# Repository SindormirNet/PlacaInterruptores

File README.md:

PlacaInterruptores
==================

  Placa de interruptores para clases de microcontroladores y electrónica digital  http://sindormir.net

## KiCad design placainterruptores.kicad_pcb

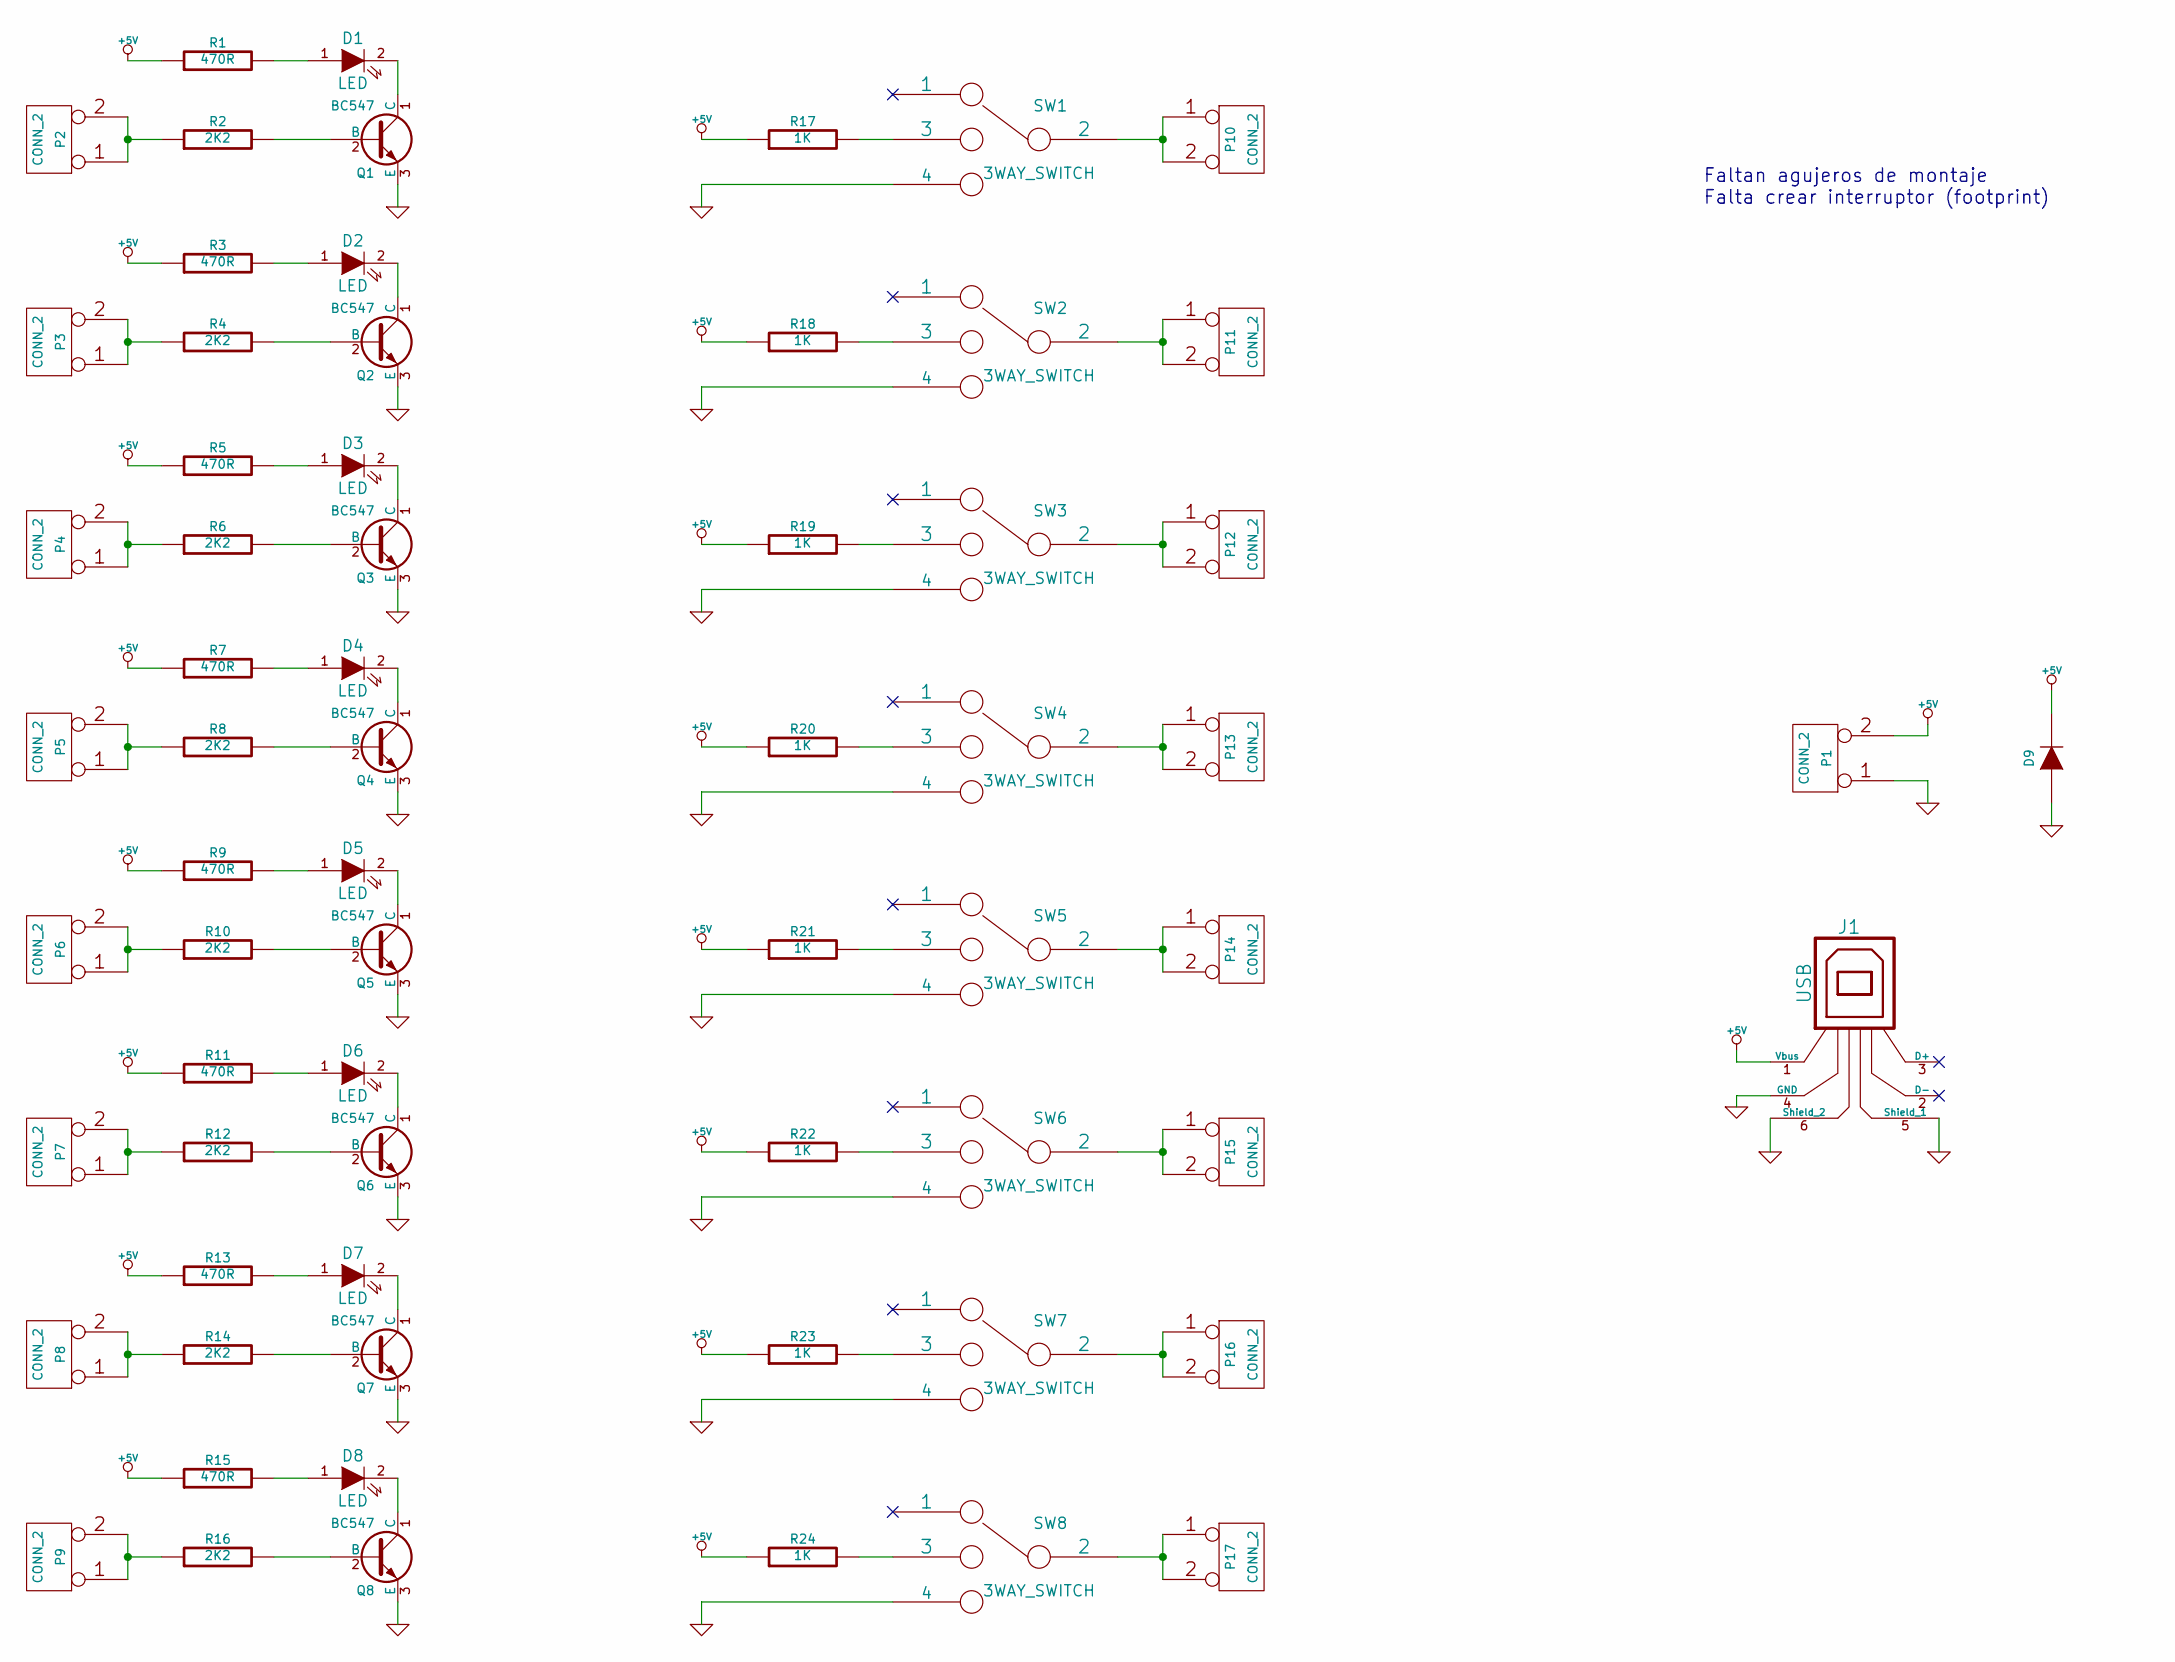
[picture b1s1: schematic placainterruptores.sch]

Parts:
D1, D2, D3, D4, D5, D6, D7, D8: LED; LED-0805
D9: DIODE; D3
J1: USB; USB_MINI_B
P1: CONN_2; 2PIN_6mm
P2, P3, P4, P5, P6, P7, P8, P9, P10, P11, P12, P13, P14, P15, P16, P17: CONN_2; SIL-2
Q1, Q2, Q3, Q4, Q5, Q6, Q7, Q8: BC547; TO92-123
R1, R3, R5, R7, R9, R11, R13, R15: 470R; R_0805
R2, R4, R6, R8, R10, R12, R14, R16: 2K2; R_0805
R17, R18, R19, R20, R21, R22, R23, R24: 1K; R_0805
SW1, SW2, SW3, SW4, SW5, SW6, SW7, SW8: 3WAY_SWITCH; 3WAY-SWITCH

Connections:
+5V: D9.2 (K), J1.1 (Vbus), P1.2 (PM), R1.1, R3.1, R5.1, R7.1, R9.1, R11.1, R13.1, R15.1, R17.1, R18.1, R19.1, R20.1, R21.1, R22.1, R23.1, R24.1
GND: D9.1 (A), J1.4 (GND), J1.5 (Shield_1), J1.6 (Shield_2), P1.1, Q1.3 (E), Q2.3 (E), Q3.3 (E), Q4.3 (E), Q5.3 (E), Q6.3 (E), Q7.3 (E), Q8.3 (E), SW1.4, SW2.4, SW3.4, SW4.4, SW5.4, SW6.4, SW7.4, SW8.4
unnamed: D1.1 (A), R1.2
unnamed: D1.2 (K), Q1.1 (C)
unnamed: D2.1 (A), R3.2
unnamed: D2.2 (K), Q2.1 (C)
unnamed: D3.1 (A), R5.2
unnamed: D3.2 (K), Q3.1 (C)
unnamed: D4.1 (A), R7.2
unnamed: D4.2 (K), Q4.1 (C)
unnamed: D5.1 (A), R9.2
unnamed: D5.2 (K), Q5.1 (C)
unnamed: D6.1 (A), R11.2
unnamed: D6.2 (K), Q6.1 (C)
unnamed: D7.1 (A), R13.2
unnamed: D7.2 (K), Q7.1 (C)
unnamed: D8.1 (A), R15.2
unnamed: D8.2 (K), Q8.1 (C)
unnamed: P2.1, P2.2 (PM), R2.1
unnamed: P3.1, P3.2 (PM), R4.1
unnamed: P4.1, P4.2 (PM), R6.1
unnamed: P5.1, P5.2 (PM), R8.1
unnamed: P6.1, P6.2 (PM), R10.1
unnamed: P7.1, P7.2 (PM), R12.1
unnamed: P8.1, P8.2 (PM), R14.1
unnamed: P9.1, P9.2 (PM), R16.1
unnamed: P10.1, P10.2 (PM), SW1.2
unnamed: P11.1, P11.2 (PM), SW2.2
unnamed: P12.1, P12.2 (PM), SW3.2
unnamed: P13.1, P13.2 (PM), SW4.2
unnamed: P14.1, P14.2 (PM), SW5.2
unnamed: P15.1, P15.2 (PM), SW6.2
unnamed: P16.1, P16.2 (PM), SW7.2
unnamed: P17.1, P17.2 (PM), SW8.2
unnamed: Q1.2 (B), R2.2
unnamed: Q2.2 (B), R4.2
unnamed: Q3.2 (B), R6.2
unnamed: Q4.2 (B), R8.2
unnamed: Q5.2 (B), R10.2
unnamed: Q6.2 (B), R12.2
unnamed: Q7.2 (B), R14.2
unnamed: Q8.2 (B), R16.2
unnamed: R17.2, SW1.3
unnamed: R18.2, SW2.3
unnamed: R19.2, SW3.3
unnamed: R20.2, SW4.3
unnamed: R21.2, SW5.3
unnamed: R22.2, SW6.3
unnamed: R23.2, SW7.3
unnamed: R24.2, SW8.3

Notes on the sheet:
Faltan agujeros de montaje Falta crear interruptor (footprint)

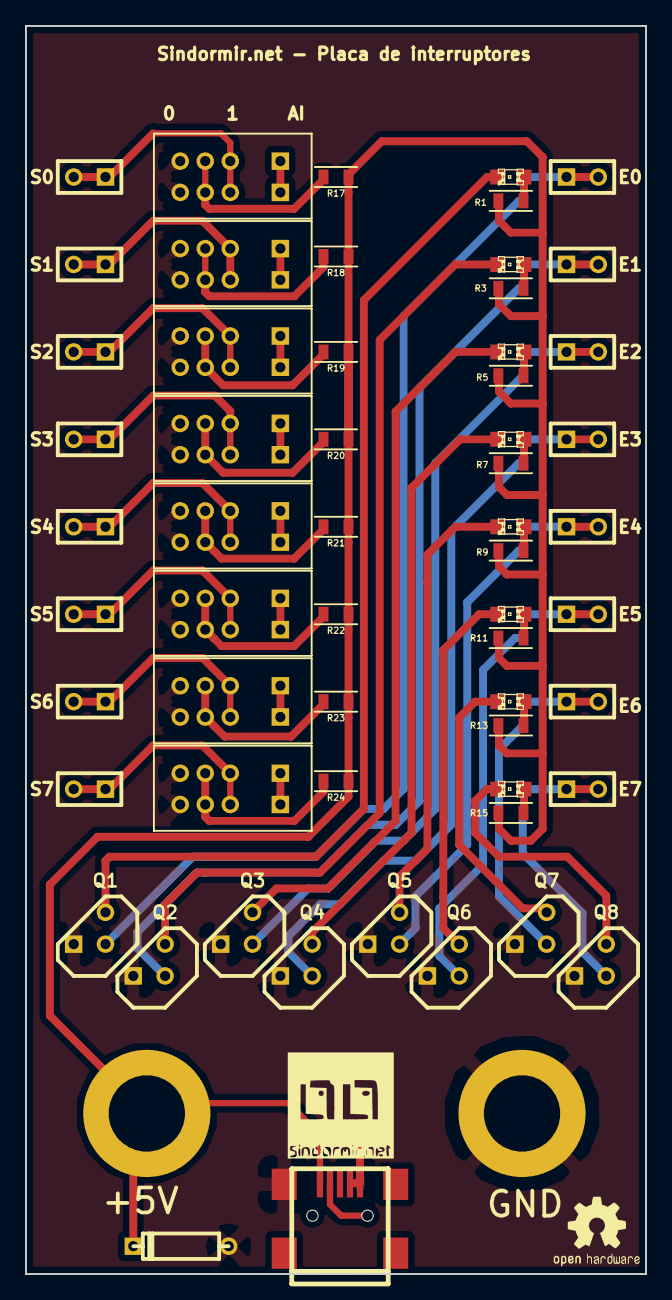
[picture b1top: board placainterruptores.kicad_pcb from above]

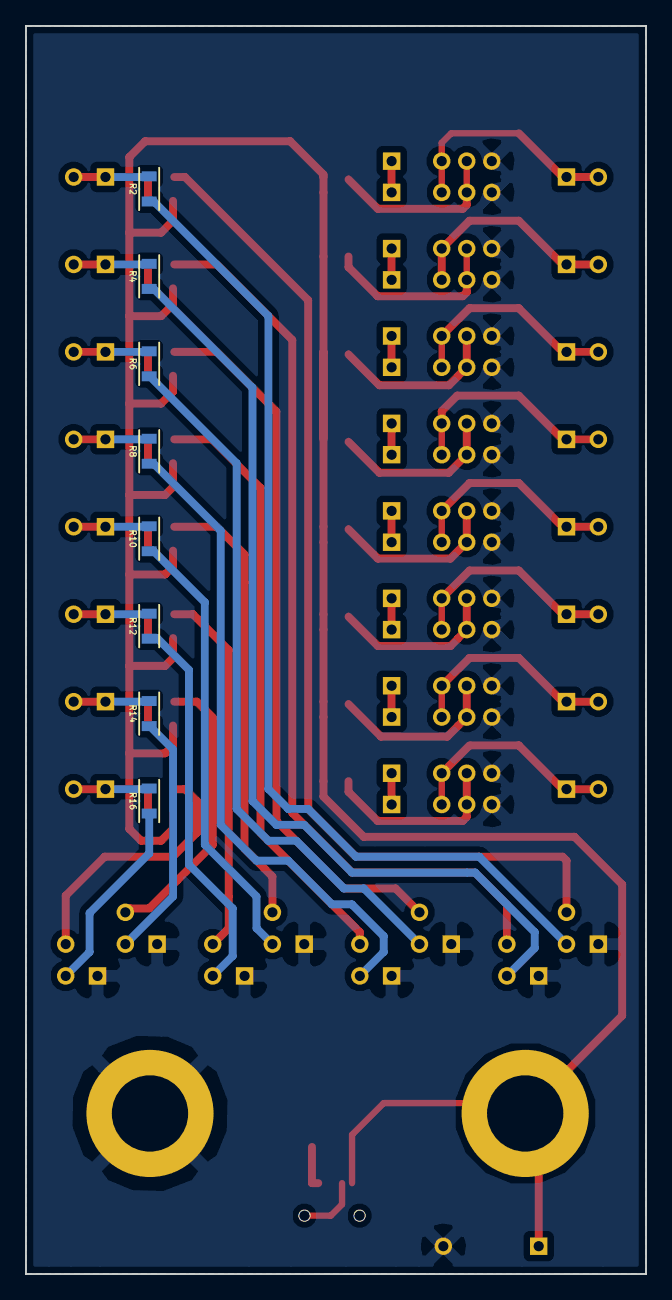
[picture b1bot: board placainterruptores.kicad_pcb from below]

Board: 2 copper layers, 49.5 x 99.7 mm, 67 parts (8 on the bottom side), 50 nets.

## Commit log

2013-09-19 Commit inicial . Versión 100% usable y fabricable
2014-09-15 Ahora no hay que pasar por HiZ para ir desde 5V a GND, lo que mejora la generación de flancos de subida/bajada. Placa adaptada para la nueva versión de Kicad. Nuevos ficheros de fabricación generados
